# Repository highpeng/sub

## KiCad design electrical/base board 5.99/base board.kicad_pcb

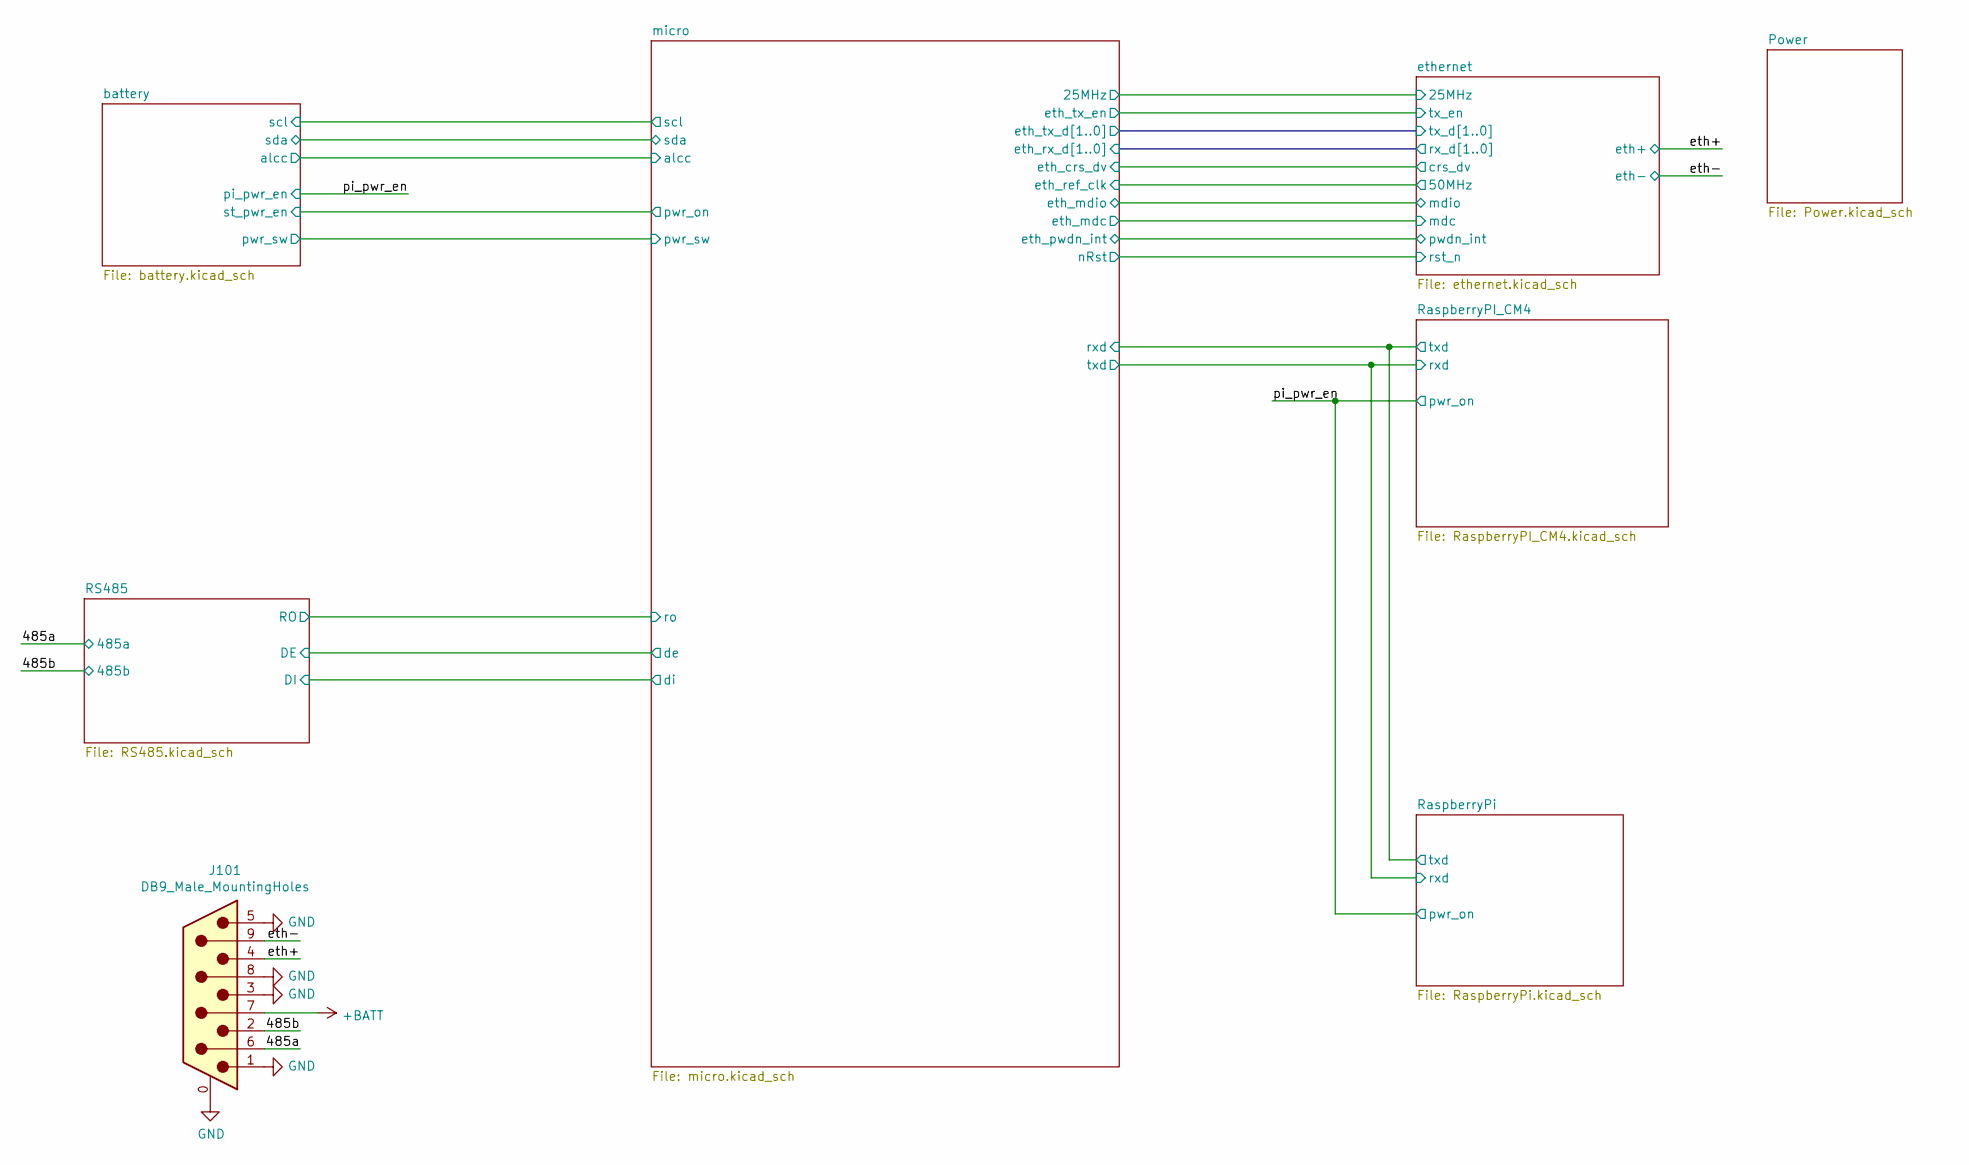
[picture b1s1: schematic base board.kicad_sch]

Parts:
J101: DB9_Male_MountingHoles; DSUB-9_Male_Horizontal_P2.77x2.84mm_EdgePinOffset9.90mm_Hou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

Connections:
+BATT: J101.7; also elsewhere on the board
/485a: J101.6; also elsewhere on the board
/485b: J101.2; also elsewhere on the board
/eth+: J101.4; also elsewhere on the board
/eth-: J101.9; also elsewhere on the board
GND: J101.0 (PAD), J101.1, J101.3, J101.5, J101.8; also elsewhere on the board

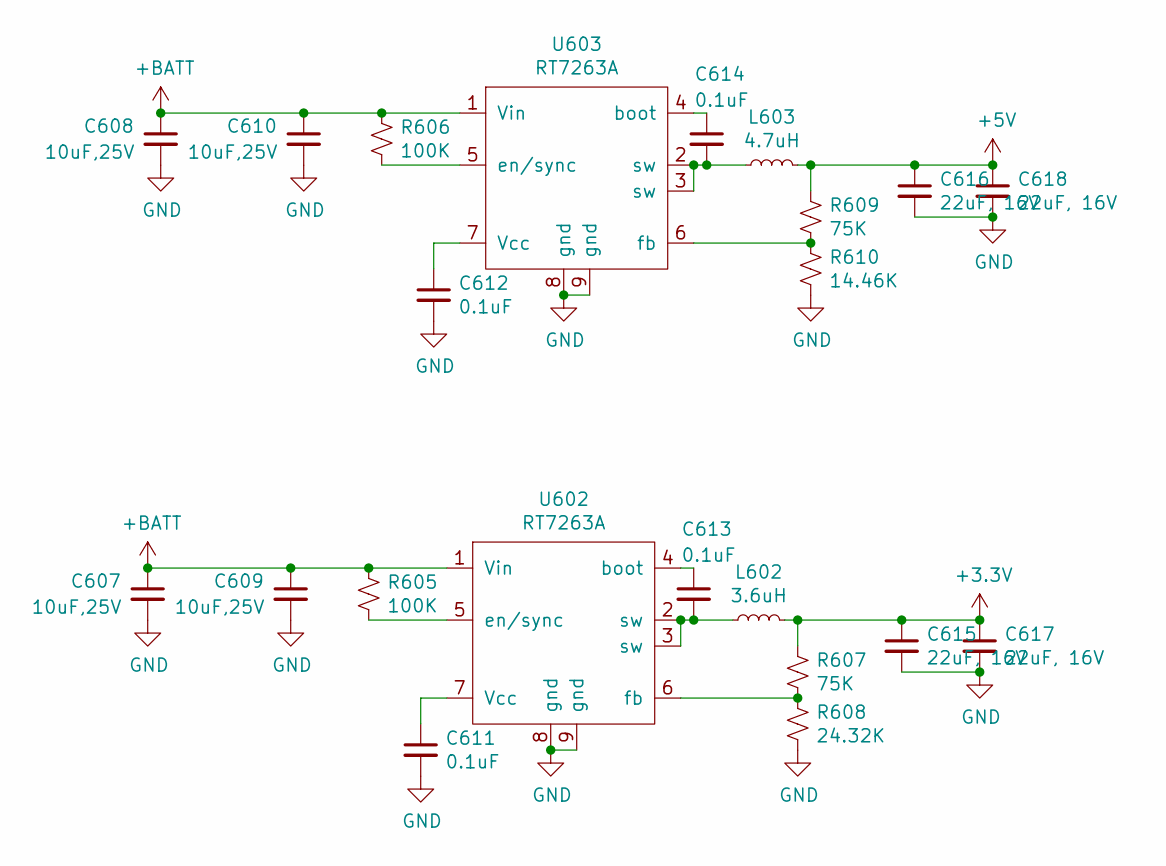
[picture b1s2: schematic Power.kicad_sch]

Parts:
C607, C608, C609, C610: 10uF,25V; C_1206_3216Metric
C611, C612, C613, C614: 0.1uF; C_0402_1005Metric
C615, C616, C617, C618: 22uF, 16V; C_1210_3225Metric
L602: 3.6uH; NR8040
L603: 4.7uH; NR8040
R605, R606: 100K; R_0402_1005Metric
R607, R609: 75K; R_0402_1005Metric
R608: 24.32K; R_0402_1005Metric
R610: 14.46K; R_0402_1005Metric
U602, U603: RT7263A; SOP-EP-8_3.9x4.9mm_P1.27mm

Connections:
+3V3: C615.1, C617.1, L602.2, R607.1; also elsewhere on the board
+5V: C616.1, C618.1, L603.2, R609.1; also elsewhere on the board
+BATT: C607.1, C608.1, C609.1, C610.1, R605.1, R606.1, U602.1 (Vin), U603.1 (Vin); also elsewhere on the board
GND: C607.2, C608.2, C609.2, C610.2, C611.2, C612.2, C615.2, C616.2, C617.2, C618.2, R608.2, R610.2, U602.8 (gnd), U602.9 (gnd), U603.8 (gnd), U603.9 (gnd); also elsewhere on the board
unnamed: C611.1, U602.7 (Vcc)
unnamed: C612.1, U603.7 (Vcc)
unnamed: C613.1, U602.4 (boot)
unnamed: C613.2, L602.1, U602.2 (sw), U602.3 (sw)
unnamed: C614.1, U603.4 (boot)
unnamed: C614.2, L603.1, U603.2 (sw), U603.3 (sw)
unnamed: R605.2, U602.5 (en/sync)
unnamed: R606.2, U603.5 (en/sync)
unnamed: R607.2, R608.1, U602.6 (fb)
unnamed: R609.2, R610.1, U603.6 (fb)

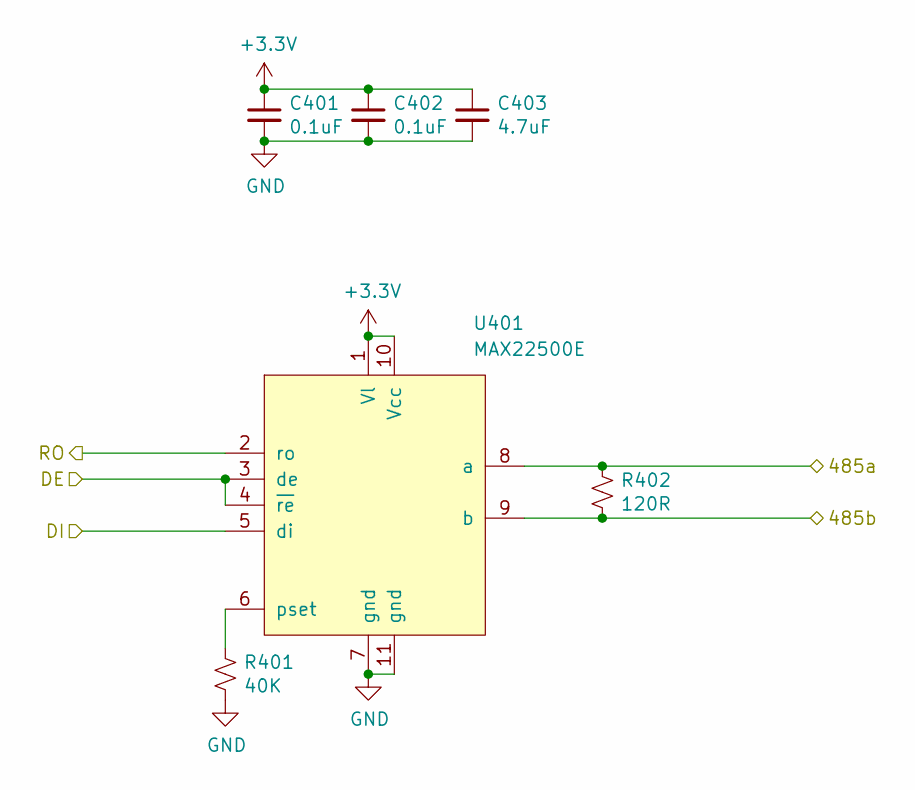
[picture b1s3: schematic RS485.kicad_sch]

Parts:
C401, C402: 0.1uF; C_0402_1005Metric
C403: 4.7uF; C_0603_1608Metric
R401: 40K; R_0402_1005Metric
R402: 120R; R_1206_3216Metric
U401: MAX22500E; DFN-10-1EP_3x3mm_P0.5mm_EP1.55x2.48mm

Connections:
+3V3: C401.1, C402.1, C403.1, U401.1 (Vl), U401.10 (Vcc); also elsewhere on the board
/485a: R402.1, U401.8 (a); also elsewhere on the board
/485b: R402.2, U401.9 (b); also elsewhere on the board
/RS485/DE: U401.3 (de~), U401.4 (~re); also elsewhere on the board
/RS485/DI: U401.5 (di); also elsewhere on the board
/RS485/RO: U401.2 (ro); also elsewhere on the board
GND: C401.2, C402.2, C403.2, R401.2, U401.7 (gnd), U401.11 (gnd); also elsewhere on the board
unnamed: R401.1, U401.6 (pset)

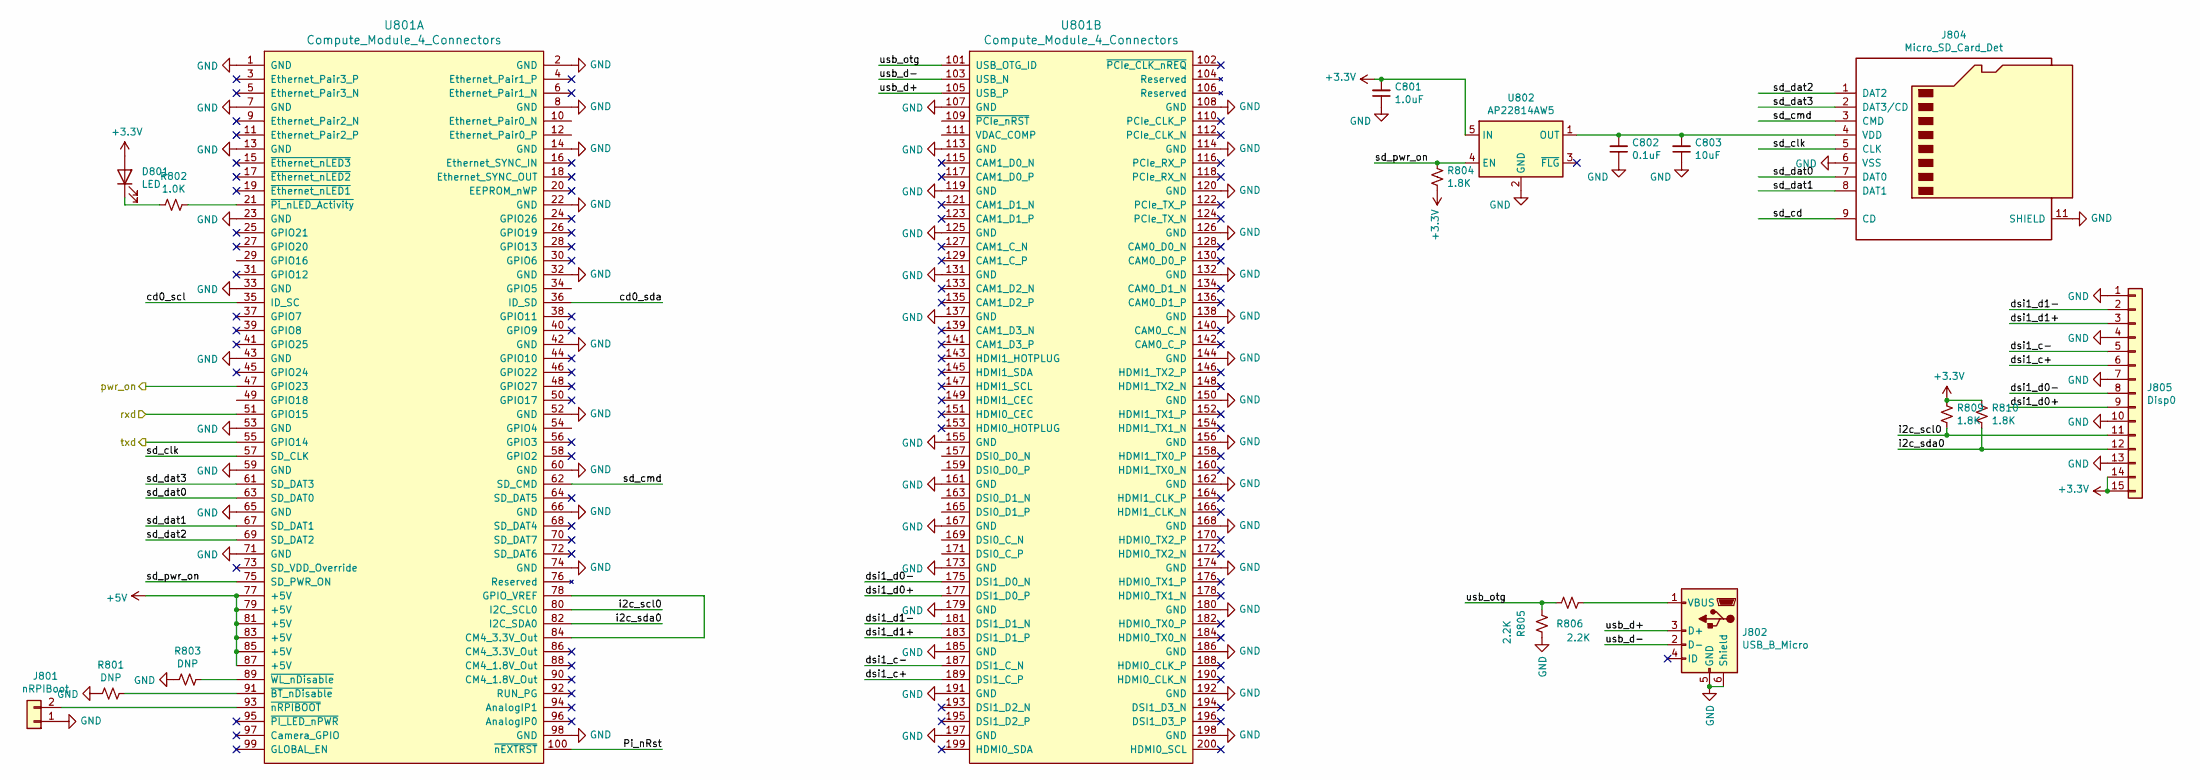
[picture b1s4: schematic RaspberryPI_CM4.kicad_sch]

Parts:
C801: 1.0uF; C_0603_1608Metric
C802: 0.1uF; C_0402_1005Metric
C803: 10uF; C_0805_2012Metric
D801: LED; LED_0402_1005Metric
J801: nRPIBoot; PinHeader_1x02_P1.27mm_Vertical
J802: USB_B_Micro; USB_Micro-B_Wuerth_629105150521
J804: Micro_SD_Card_Det; MEM2061
J805: Disp0; Molex_200528-0150_1x15-1MP_P1.00mm_Horizontal
R801, R803: DNP; R_0402_1005Metric
R802: 1.0K; R_0402_1005Metric
R804, R809, R810: 1.8K; R_0402_1005Metric
R805, R806: 2.2K; R_0402_1005Metric
U801: Compute_Module_4_Connectors; CM4
U802: AP22814AW5; SOT-23-5

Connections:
+3V3: C801.2, D801.2 (A), J805.14, J805.15, R804.2, R809.1, R810.1, U802.5 (IN); also elsewhere on the board
+5V: U801.77 (+5V), U801.79 (+5V), U801.81 (+5V), U801.83 (+5V), U801.85 (+5V), U801.87 (+5V); also elsewhere on the board
/RaspberryPI_CM4/Pi_nRst: U801.100 (~nEXTRST)
/RaspberryPI_CM4/cd0_scl: U801.35 (ID_SC)
/RaspberryPI_CM4/cd0_sda: U801.36 (ID_SD)
/RaspberryPI_CM4/dsi1_c+: J805.6, U801.189 (DSI1_C_P)
/RaspberryPI_CM4/dsi1_c-: J805.5, U801.187 (DSI1_C_N)
/RaspberryPI_CM4/dsi1_d0+: J805.9, U801.177 (DSI1_D0_P)
/RaspberryPI_CM4/dsi1_d0-: J805.8, U801.175 (DSI1_D0_N)
/RaspberryPI_CM4/dsi1_d1+: J805.3, U801.183 (DSI1_D1_P)
/RaspberryPI_CM4/dsi1_d1-: J805.2, U801.181 (DSI1_D1_N)
/RaspberryPI_CM4/i2c_scl0: J805.11, R809.2, U801.80 (I2C_SCL0)
/RaspberryPI_CM4/i2c_sda0: J805.12, R810.2, U801.82 (I2C_SDA0)
/RaspberryPI_CM4/rxd: U801.51 (GPIO15); also elsewhere on the board
/RaspberryPI_CM4/sd_cd: J804.9 (CD)
/RaspberryPI_CM4/sd_clk: J804.5 (CLK), U801.57 (SD_CLK)
/RaspberryPI_CM4/sd_cmd: J804.3 (CMD), U801.62 (SD_CMD)
/RaspberryPI_CM4/sd_dat0: J804.7 (DAT0), U801.63 (SD_DAT0)
/RaspberryPI_CM4/sd_dat1: J804.8 (DAT1), U801.67 (SD_DAT1)
/RaspberryPI_CM4/sd_dat2: J804.1 (DAT2), U801.69 (SD_DAT2)
/RaspberryPI_CM4/sd_dat3: J804.2 (DAT3/CD), U801.61 (SD_DAT3)
/RaspberryPI_CM4/sd_pwr_on: R804.1, U801.75 (SD_PWR_ON), U802.4 (EN)
/RaspberryPI_CM4/txd: U801.55 (GPIO14); also elsewhere on the board
/RaspberryPI_CM4/usb_d+: J802.3 (D+), U801.105 (USB_P)
/RaspberryPI_CM4/usb_d-: J802.2 (D-), U801.103 (USB_N)
/RaspberryPI_CM4/usb_otg: R805.1, R806.1, U801.101 (USB_OTG_ID)
/pi_pwr_en: U801.47 (GPIO23); also elsewhere on the board
GND: C801.1, C802.1, C803.1, J801.1, J802.5 (GND), J802.6 (Shield), J804.6 (VSS), J804.11 (SHIELD), J805.1, J805.4, J805.7, J805.10, J805.13, R801.2, R803.2, R805.2, U801.1 (GND), U801.2 (GND), U801.7 (GND), U801.8 (GND), U801.13 (GND), U801.14 (GND), U801.22 (GND), U801.23 (GND), U801.32 (GND), U801.33 (GND), U801.42 (GND), U801.43 (GND), U801.52 (GND), U801.53 (GND), U801.59 (GND), U801.60 (GND), U801.65 (GND), U801.66 (GND), U801.71 (GND), U801.74 (GND), U801.98 (GND), U801.107 (GND), U801.108 (GND), U801.113 (GND), U801.114 (GND), U801.119 (GND), U801.120 (GND), U801.125 (GND), U801.126 (GND), U801.131 (GND), U801.132 (GND), U801.137 (GND), U801.138 (GND), U801.144 (GND), U801.150 (GND), U801.155 (GND), U801.156 (GND), U801.161 (GND), U801.162 (GND), U801.167 (GND), U801.168 (GND), U801.173 (GND), U801.174 (GND), U801.179 (GND), U801.180 (GND), U801.185 (GND), U801.186 (GND), U801.191 (GND), U801.192 (GND), U801.197 (GND), U801.198 (GND), U802.2 (GND); also elsewhere on the board
unnamed: C802.2, C803.2, J804.4 (VDD), U802.1 (OUT)
unnamed: D801.1 (K), R802.2
unnamed: J801.2, U801.93 (~nRPIBOOT)
unnamed: J802.1 (VBUS), R806.2
unnamed: R801.1, U801.91 (~BT_nDisable)
unnamed: R802.1, U801.21 (~Pi_nLED_Activity)
unnamed: R803.1, U801.89 (~WL_nDisable)
unnamed: U801.78 (GPIO_VREF), U801.84 (CM4_3.3V_Out)

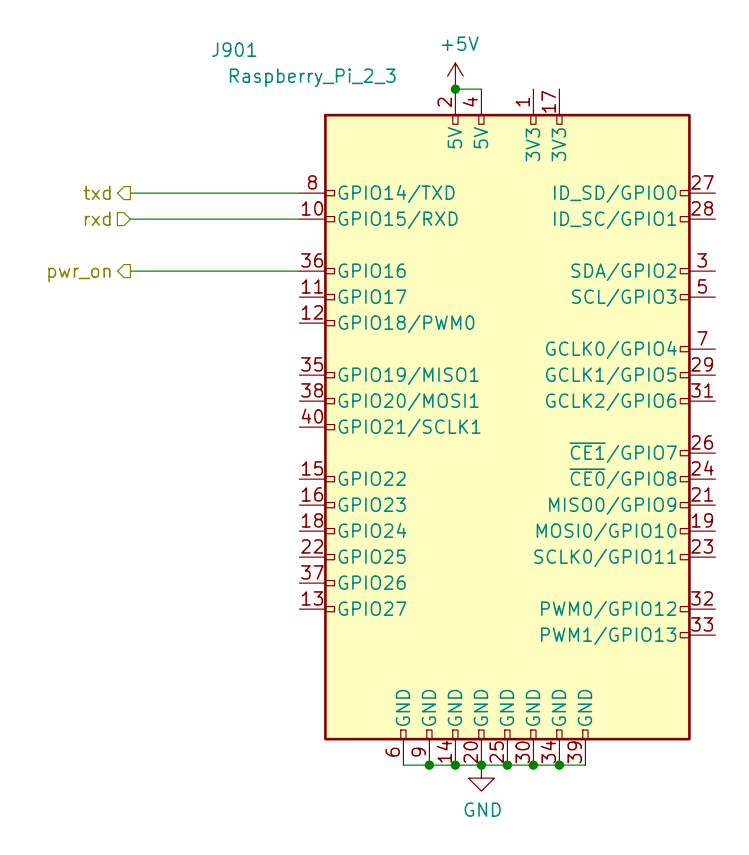
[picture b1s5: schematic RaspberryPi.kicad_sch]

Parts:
J901: Raspberry_Pi_2_3; MODULE_RASPBERRY_PI_3_MODEL_B+

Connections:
+5V: J901.2 (5V), J901.4 (5V); also elsewhere on the board
/RaspberryPI_CM4/rxd: J901.10 (GPIO15/RXD); also elsewhere on the board
/RaspberryPI_CM4/txd: J901.8 (GPIO14/TXD); also elsewhere on the board
/pi_pwr_en: J901.36 (GPIO16); also elsewhere on the board
GND: J901.6 (GND), J901.9 (GND), J901.14 (GND), J901.20 (GND), J901.25 (GND), J901.30 (GND), J901.34 (GND), J901.39 (GND); also elsewhere on the board

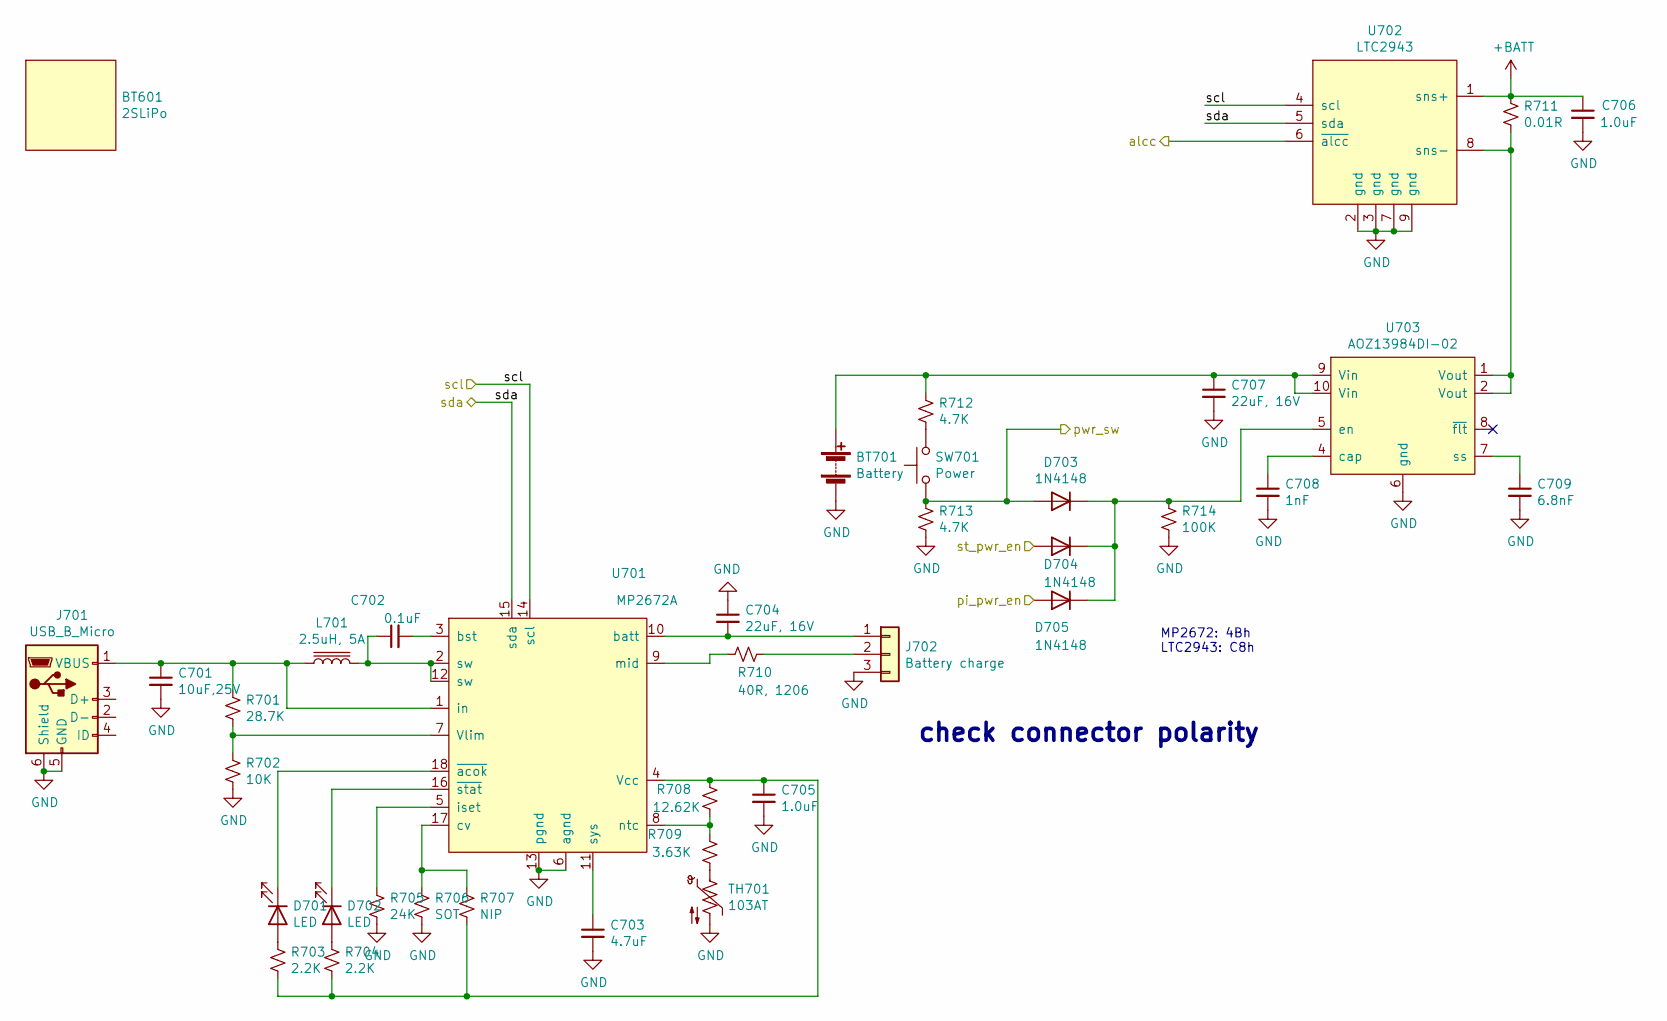
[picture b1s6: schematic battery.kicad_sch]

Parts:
BT601: 2SLiPo
BT701: Battery; AMASS_XT60-M
C701: 10uF,25V; C_1206_3216Metric
C702: 0.1uF; C_0402_1005Metric
C703: 4.7uF; C_0603_1608Metric
C704, C707: 22uF, 16V; C_1210_3225Metric
C705, C706: 1.0uF; C_0603_1608Metric
C708: 1nF; C_0402_1005Metric
C709: 6.8nF; C_0402_1005Metric
D701, D702: LED; LED_0402_1005Metric
D703, D704, D705: 1N4148; D_SOD-123
J701: USB_B_Micro; USB_Micro-B_Wuerth_629105150521
J702: Battery charge; JST_XH_B3B-XH-AM_1x03_P2.50mm_Vertical
L701: 2.5uH, 5A; CDRH8D38
R701: 28.7K; R_0402_1005Metric
R702: 10K; R_0402_1005Metric
R703, R704: 2.2K; R_0402_1005Metric
R705: 24K; R_0402_1005Metric
R706: SOT; R_0402_1005Metric
R707: NIP; R_0402_1005Metric
R708: 12.62K; R_0402_1005Metric
R709: 3.63K; R_0402_1005Metric
R710: 40R, 1206; R_1206_3216Metric
R711: 0.01R; R_0805_2012Metric
R712, R713: 4.7K; R_0402_1005Metric
R714: 100K; R_0402_1005Metric
SW701: Power; evqpf
TH701: 103AT; Hirose_DF13C_CL535-0402-2-51_1x02-1MP_P1.25mm_Vertical
U701: MP2672A; QFN-18
U702: LTC2943; DFN-8-1EP_3x3mm_P0.5mm_EP1.66x2.38mm
U703: AOZ13984DI-02; DFN3x3-12L

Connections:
+BATT: C706.1, R711.1, U702.1 (sns+); also elsewhere on the board
/battery/alcc: U702.6 (~alcc); also elsewhere on the board
/battery/pwr_sw: D703.2 (A), R713.1, SW701.1; also elsewhere on the board
/battery/scl: U701.14 (scl), U702.4 (scl); also elsewhere on the board
/battery/sda: U701.15 (sda), U702.5 (sda); also elsewhere on the board
/battery/st_pwr_en: D704.2 (A); also elsewhere on the board
/pi_pwr_en: D705.2 (A); also elsewhere on the board
GND: BT701.2 (-), C701.2, C703.2, C704.1, C705.2, C706.2, C707.2, C708.2, C709.2, J701.5 (GND), J701.6 (Shield), J702.3, R702.2, R705.2, R706.2, R713.2, R714.2, TH701.2, U701.6 (agnd), U701.13 (pgnd), U702.2 (gnd), U702.3 (gnd), U702.7 (gnd), U702.9 (gnd), U703.6 (gnd); also elsewhere on the board
unnamed: BT701.1 (+), C707.1, R712.1, U703.9 (Vin), U703.10 (Vin)
unnamed: C701.1, J701.1 (VBUS), L701.1, R701.1, U701.1 (in)
unnamed: C702.1, L701.2, U701.2 (sw), U701.12 (sw)
unnamed: C702.2, U701.3 (bst)
unnamed: C703.1, U701.11 (sys)
unnamed: C704.2, J702.1, U701.10 (batt)
unnamed: C705.1, R703.2, R704.2, R707.2, R708.2, U701.4 (Vcc)
unnamed: C708.1, U703.4 (cap)
unnamed: C709.1, U703.7 (ss)
unnamed: D701.1 (K), U701.18 (~acok)
unnamed: D701.2 (A), R703.1
unnamed: D702.1 (K), U701.16 (~stat)
unnamed: D702.2 (A), R704.1
unnamed: D703.1 (K), D704.1 (K), D705.1 (K), R714.1, U703.5 (en)
unnamed: J702.2, R710.1
unnamed: R701.2, R702.1, U701.7 (Vlim)
unnamed: R705.1, U701.5 (iset)
unnamed: R706.1, R707.1, U701.17 (cv)
unnamed: R708.1, R709.2, U701.8 (ntc)
unnamed: R709.1, TH701.1
unnamed: R710.2, U701.9 (mid)
unnamed: R711.2, U702.8 (sns-), U703.1 (Vout), U703.2 (Vout)
unnamed: R712.2, SW701.2

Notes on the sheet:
check connector polarity
MP2672: 4Bh LTC2943: C8h

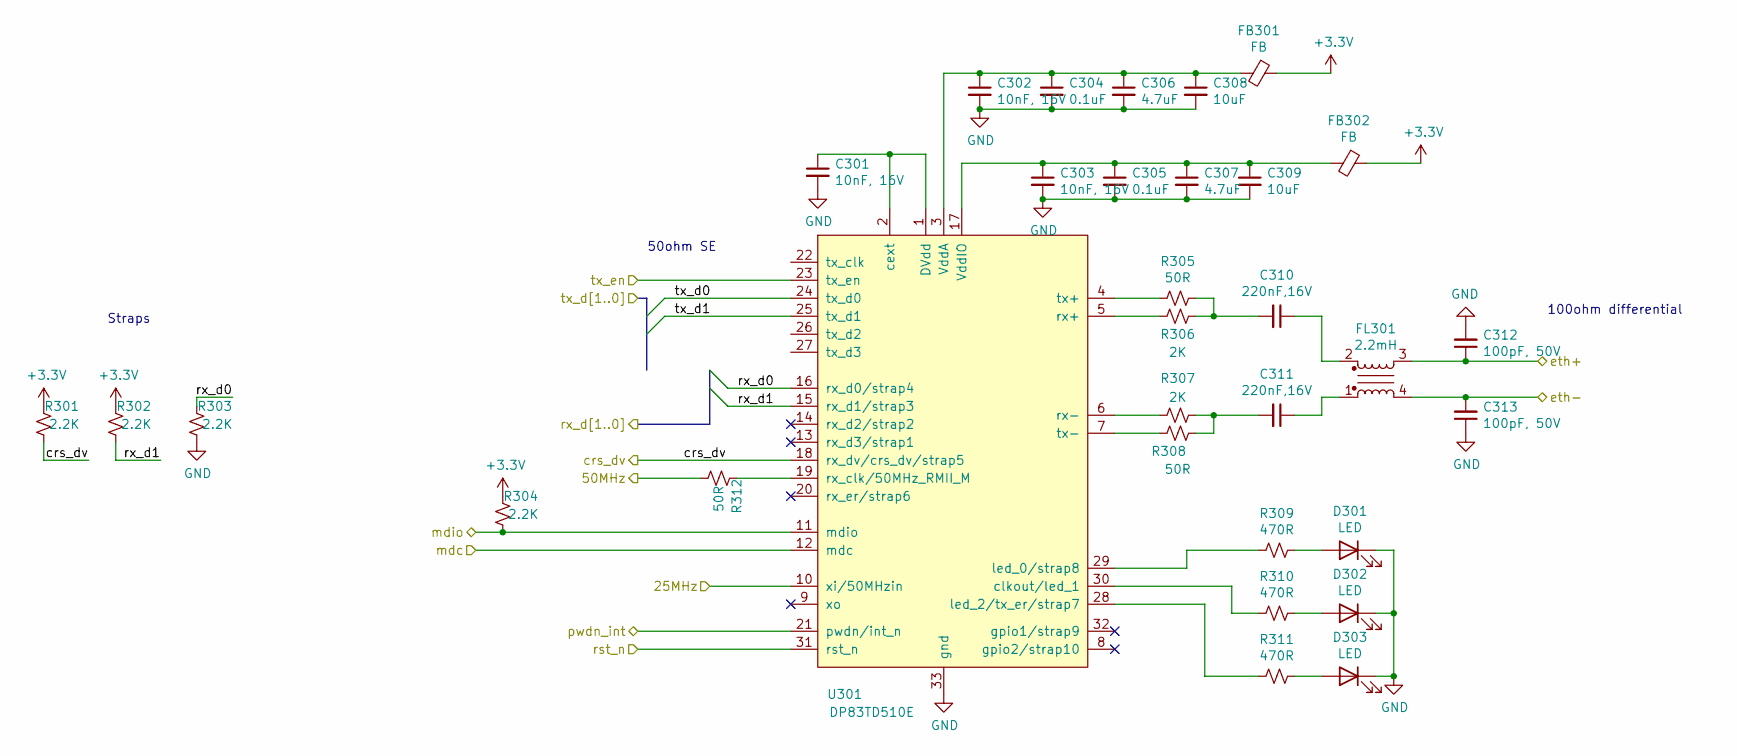
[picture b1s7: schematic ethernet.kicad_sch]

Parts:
C301, C302, C303: 10nF, 16V; C_0402_1005Metric
C304, C305: 0.1uF; C_0402_1005Metric
C306, C307: 4.7uF; C_0603_1608Metric
C308, C309: 10uF; C_0805_2012Metric
C310, C311: 220nF,16V; C_0603_1608Metric
C312, C313: 100pF, 50V; C_0603_1608Metric
D301, D302, D303: LED; LED_0402_1005Metric
FB301, FB302: FB; R_0603_1608Metric
FL301: 2.2mH; L_WE_SL5
R301, R302, R303, R304: 2.2K; R_0402_1005Metric
R305, R308, R312: 50R; R_0402_1005Metric
R306, R307: 2K; R_2512_6332Metric
R309, R310, R311: 470R; R_0402_1005Metric
U301: DP83TD510E; TQFN-32-1EP_5x5mm_P0.5mm_EP2.1x2.1mm

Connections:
+3V3: FB301.1, FB302.1, R301.2, R302.2, R304.2; also elsewhere on the board
/eth+: C312.1, FL301.3; also elsewhere on the board
/eth-: C313.2, FL301.4; also elsewhere on the board
/ethernet/25MHz: U301.10 (xi/50MHzin); also elsewhere on the board
/ethernet/50MHz: R312.1; also elsewhere on the board
/ethernet/crs_dv: R301.1, U301.18 (rx_dv/crs_dv/strap5); also elsewhere on the board
/ethernet/mdc: U301.12 (mdc); also elsewhere on the board
/ethernet/mdio: R304.1, U301.11 (mdio); also elsewhere on the board
/ethernet/pwdn_int: U301.21 (pwdn/int_n); also elsewhere on the board
/ethernet/tx_en: U301.23 (tx_en); also elsewhere on the board
/micro/eth_rx_d0: R303.2, U301.16 (rx_d0/strap4); also elsewhere on the board
/micro/eth_rx_d1: R302.1, U301.15 (rx_d1/strap3); also elsewhere on the board
/micro/eth_tx_d0: U301.24 (tx_d0); also elsewhere on the board
/micro/eth_tx_d1: U301.25 (tx_d1); also elsewhere on the board
/micro/nrst: U301.31 (rst_n); also elsewhere on the board
GND: C301.2, C302.2, C303.2, C304.2, C305.2, C306.2, C307.2, C308.2, C309.2, C312.2, C313.1, D301.1 (K), D302.1 (K), D303.1 (K), R303.1, U301.33 (gnd); also elsewhere on the board
unnamed: C301.1, U301.1 (DVdd), U301.2 (cext)
unnamed: C302.1, C304.1, C306.1, C308.1, FB301.2, U301.3 (VddA)
unnamed: C303.1, C305.1, C307.1, C309.1, FB302.2, U301.17 (VddIO)
unnamed: C310.1, FL301.2
unnamed: C310.2, R305.1, R306.1
unnamed: C311.1, FL301.1
unnamed: C311.2, R307.1, R308.1
unnamed: R305.2, U301.4 (tx+)
unnamed: R306.2, U301.5 (rx+)
unnamed: R307.2, U301.6 (rx-)
unnamed: R308.2, U301.7 (tx-)
unnamed: D301.2 (A), R309.1
unnamed: D302.2 (A), R310.1
unnamed: D303.2 (A), R311.1
unnamed: R312.2, U301.19 (rx_clk/50MHz_RMII_M)
unnamed: R311.2, U301.28 (led_2/tx_er/strap7)
unnamed: R309.2, U301.29 (led_0/strap8)
unnamed: R310.2, U301.30 (clkout/led_1)

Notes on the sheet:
Straps
50ohm SE
100ohm differential

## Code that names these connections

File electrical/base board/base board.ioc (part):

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Mcu.Name=STM32F217I(E-G)Tx
Mcu.Package=LQFP176
Mcu.UserName=STM32F217IETx
PA1.Mode=RMII
PA1.Signal=ETH_REF_CLK
PA11.Mode=Device_Only
PA11.Signal=USB_OTG_FS_DM
PA12.Mode=Device_Only
PA12.Signal=USB_OTG_FS_DP
PA13.Mode=JTAG_5_pins
PA13.Signal=SYS_JTMS-SWDIO
PA14.Mode=JTAG_5_pins
PA14.Signal=SYS_JTCK-SWCLK
PA15.Mode=JTAG_5_pins
PA15.Signal=SYS_JTDI
PA2.Mode=RMII
PA2.Signal=ETH_MDIO
PA3.Mode=Device_HS
PA3.Signal=USB_OTG_HS_ULPI_D0
PA5.Mode=Device_HS
PA5.Signal=USB_OTG_HS_ULPI_CK
PA6.GPIOParameters=GPIO_Label
PA6.GPIO_Label=fan
PA6.Signal=S_TIM13_CH1
PA7.Mode=RMII
PA7.Signal=ETH_CRS_DV
PA8.Mode=Clock-out-1
PA8.Signal=RCC_MCO_1
PA9.Mode=Activate_VBUS
PA9.Signal=USB_OTG_FS_VBUS
PB0.Mode=Device_HS
PB0.Signal=USB_OTG_HS_ULPI_D1
PB1.Mode=Device_HS
PB1.Signal=USB_OTG_HS_ULPI_D2
PB10.Mode=Device_HS
PB10.Signal=USB_OTG_HS_ULPI_D3
PB11.Mode=Device_HS
PB11.Signal=USB_OTG_HS_ULPI_D4
PB12.Mode=Device_HS
PB12.Signal=USB_OTG_HS_ULPI_D5
PB13.Mode=Device_HS
PB13.Signal=USB_OTG_HS_ULPI_D6
PB3.Mode=JTAG_5_pins
PB3.Signal=SYS_JTDO-SWO
PB4.Mode=JTAG_5_pins
PB4.Signal=SYS_JTRST
PB5.Mode=Device_HS
PB5.Signal=USB_OTG_HS_ULPI_D7
PB6.Mode=I2C
PB6.Signal=I2C1_SCL
PB7.Mode=I2C
PB7.Signal=I2C1_SDA
PB8.GPIOParameters=GPIO_Label
PB8.GPIO_Label=alcc
PB8.Signal=GPIO_Input
PB9.GPIOParameters=GPIO_Label
PB9.GPIO_Label=buzzer
PB9.Signal=S_TIM11_CH1
PC0.Mode=Device_HS
PC0.Signal=USB_OTG_HS_ULPI_STP
PC1.Mode=RMII
PC1.Signal=ETH_MDC
PC15-OSC32_OUT.GPIOParameters=GPIO_Label
PC15-OSC32_OUT.GPIO_Label=led
PC15-OSC32_OUT.Signal=GPIO_Output
PC2.Signal=ADCx_IN12
PC3.Signal=ADCx_IN13
PC4.Mode=RMII
PC4.Signal=ETH_RXD0
PC5.Mode=RMII
PC5.Signal=ETH_RXD1
PD5.Mode=Asynchronous
PD5.Signal=USART2_TX
PD6.Mode=Asynchronous
PD6.Signal=USART2_RX
PE2.GPIOParameters=GPIO_Label
PE2.GPIO_Label=joy1s
PE2.Signal=GPIO_Input
PE3.GPIOParameters=GPIO_Label
PE3.GPIO_Label=joy2s
PE3.Signal=GPIO_Input
PE4.GPIOParameters=GPIO_Label
PE4.GPIO_Label=joy3s
PE4.Signal=GPIO_Input
PE5.GPIOParameters=GPIO_Label
PE5.GPIO_Label=joy4s
PE5.Signal=GPIO_Input
PF0.GPIOParameters=GPIO_Pu
PF0.GPIO_Pu=GPIO_PULLUP
PF0.Mode=I2C
PF0.Signal=I2C2_SDA
PF1.GPIOParameters=GPIO_Pu
PF1.GPIO_Pu=GPIO_PULLUP
PF1.Mode=I2C
PF1.Signal=I2C2_SCL
PF10.GPIOParameters=GPIO_Label
PF10.GPIO_Label=joy4b
PF10.Mode=IN8
PF10.Signal=ADC3_IN8
PF3.GPIOParameters=GPIO_Label
PF3.GPIO_Label=joy1a
PF3.Mode=IN9
PF3.Signal=ADC3_IN9
PF4.GPIOParameters=GPIO_Label
PF4.GPIO_Label=joy1b
PF4.Mode=IN14
PF4.Signal=ADC3_IN14
PF5.GPIOParameters=GPIO_Label
PF5.GPIO_Label=joy2a
PF5.Mode=IN15
PF5.Signal=ADC3_IN15
PF6.GPIOParameters=GPIO_Label
PF6.GPIO_Label=joy2b
PF6.Mode=IN4
PF6.Signal=ADC3_IN4
PF7.GPIOParameters=GPIO_Label
PF7.GPIO_Label=joy3a
PF7.Mode=IN5
PF7.Signal=ADC3_IN5
PF8.GPIOParameters=GPIO_Label
PF8.GPIO_Label=joy3b
PF8.Mode=IN6
PF8.Signal=ADC3_IN6
PF9.GPIOParameters=GPIO_Label
PF9.GPIO_Label=joy4a
PF9.Mode=IN7
PF9.Signal=ADC3_IN7
PG11.Mode=RMII
PG11.Signal=ETH_TX_EN
PG13.Mode=RMII
PG13.Signal=ETH_TXD0
PG14.Mode=RMII
PG14.Signal=ETH_TXD1
PH0-OSC_IN.Mode=HSE-External-Clock-Source
PH0-OSC_IN.Signal=RCC_OSC_IN
PH1-OSC_OUT.Mode=HSE-External-Clock-Source
PH1-OSC_OUT.Signal=RCC_OSC_OUT
PH4.Mode=Device_HS
PH4.Signal=USB_OTG_HS_ULPI_NXT
PI11.Mode=Device_HS
PI11.Signal=USB_OTG_HS_ULPI_DIR
RCC.HSE_VALUE=25000000
RCC.SYSCLKFreq_VALUE=120000000
RCC.SYSCLKSource=RCC_SYSCLKSOURCE_PLLCLK
board=custom

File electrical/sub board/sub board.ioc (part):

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Mcu.Name=STM32F217I(E-G)Tx
Mcu.Package=LQFP176
Mcu.UserName=STM32F217IETx
PA0-WKUP.Signal=S_TIM2_CH1_ETR
PA1.Mode=RMII
PA1.Signal=ETH_REF_CLK
PA11.Mode=Device_Only
PA11.Signal=USB_OTG_FS_DM
PA12.Mode=Device_Only
PA12.Signal=USB_OTG_FS_DP
PA13.Mode=JTAG_5_pins
PA13.Signal=SYS_JTMS-SWDIO
PA14.Mode=JTAG_5_pins
PA14.Signal=SYS_JTCK-SWCLK
PA15.Mode=JTAG_5_pins
PA15.Signal=SYS_JTDI
PA2.Mode=RMII
PA2.Signal=ETH_MDIO
PA3.Mode=Device_HS
PA3.Signal=USB_OTG_HS_ULPI_D0
PA5.Mode=Device_HS
PA5.Signal=USB_OTG_HS_ULPI_CK
PA7.Mode=RMII
PA7.Signal=ETH_CRS_DV
PA8.Mode=Clock-out-1
PA8.Signal=RCC_MCO_1
PA9.Mode=Activate_VBUS
PA9.Signal=USB_OTG_FS_VBUS
PB0.Mode=Device_HS
PB0.Signal=USB_OTG_HS_ULPI_D1
PB1.Mode=Device_HS
PB1.Signal=USB_OTG_HS_ULPI_D2
PB10.Mode=Device_HS
PB10.Signal=USB_OTG_HS_ULPI_D3
PB11.Mode=Device_HS
PB11.Signal=USB_OTG_HS_ULPI_D4
PB12.Mode=Device_HS
PB12.Signal=USB_OTG_HS_ULPI_D5
PB13.Mode=Device_HS
PB13.Signal=USB_OTG_HS_ULPI_D6
PB14.Mode=Full_Duplex_Master
PB14.Signal=SPI2_MISO
PB15.Mode=Full_Duplex_Master
PB15.Signal=SPI2_MOSI
PB3.Mode=JTAG_5_pins
PB3.Signal=SYS_JTDO-SWO
PB4.Mode=JTAG_5_pins
PB4.Signal=SYS_JTRST
PB5.Mode=Device_HS
PB5.Signal=USB_OTG_HS_ULPI_D7
PB6.Mode=I2C
PB6.Signal=I2C1_SCL
PB7.Mode=I2C
PB7.Signal=I2C1_SDA
PB8.GPIOParameters=GPIO_Label
PB8.GPIO_Label=sonar_clk
PB8.Signal=S_TIM10_CH1
PB9.Mode=NSS_Signal_Hard_Input
PB9.Signal=SPI2_NSS
PC0.Mode=Device_HS
PC0.Signal=USB_OTG_HS_ULPI_STP
PC1.Mode=RMII
PC1.Signal=ETH_MDC
PC10.Mode=SD_4_bits_Wide_bus
PC10.Signal=SDIO_D2
PC11.Mode=SD_4_bits_Wide_bus
PC11.Signal=SDIO_D3
PC12.Mode=SD_4_bits_Wide_bus
PC12.Signal=SDIO_CK
PC13.Signal=GPIO_Input
PC15-OSC32_OUT.GPIOParameters=GPIO_Label
PC15-OSC32_OUT.GPIO_Label=led
PC15-OSC32_OUT.Signal=GPIO_Output
PC2.Signal=ADCx_IN12
PC4.Mode=RMII
PC4.Signal=ETH_RXD0
PC5.Mode=RMII
PC5.Signal=ETH_RXD1
PC6.GPIOParameters=GPIO_Label
PC6.GPIO_Label=sonar_out3
PC6.Signal=S_TIM8_CH1
PC7.GPIOParameters=GPIO_Label
PC7.GPIO_Label=sonar_out4
PC7.Signal=S_TIM8_CH2
PC8.Mode=SD_4_bits_Wide_bus
PC8.Signal=SDIO_D0
PC9.Mode=SD_4_bits_Wide_bus
PC9.Signal=SDIO_D1
PD12.GPIOParameters=GPIO_Label
PD12.GPIO_Label=bdlc0
PD12.Signal=S_TIM4_CH1
PD13.GPIOParameters=GPIO_Label
PD13.GPIO_Label=bdlc1
PD13.Signal=S_TIM4_CH2
PD14.GPIOParameters=GPIO_Label
PD14.GPIO_Label=bdlc2
PD14.Signal=S_TIM4_CH3
PD15.GPIOParameters=GPIO_Label
PD15.GPIO_Label=bdlc3
PD15.Signal=S_TIM4_CH4
PD2.Mode=SD_4_bits_Wide_bus
PD2.Signal=SDIO_CMD
PD4.Mode=RTS_Only
PD4.Signal=USART2_RTS
PD5.Mode=Asynchronous
PD5.Signal=USART2_TX
PD6.Mode=Asynchronous
PD6.Signal=USART2_RX
PD8.Mode=Asynchronous
PD8.Signal=USART3_TX
PD9.Mode=Asynchronous
PD9.Signal=USART3_RX
PE11.GPIOParameters=GPIO_Label
PE11.GPIO_Label=servo1
PE11.Signal=S_TIM1_CH2
PE13.GPIOParameters=GPIO_Label
PE13.GPIO_Label=servo2
PE13.Signal=S_TIM1_CH3
PE14.GPIOParameters=GPIO_Label
PE14.GPIO_Label=servo3
PE14.Signal=S_TIM1_CH4
PE5.GPIOParameters=GPIO_Label
PE5.GPIO_Label=lights
PE5.Signal=S_TIM9_CH1
PE9.GPIOParameters=GPIO_Label
PE9.GPIO_Label=servo0
PE9.Signal=S_TIM1_CH1
PF0.Mode=I2C
PF0.Signal=I2C2_SDA
PF1.Mode=I2C
PF1.Signal=I2C2_SCL
PF2.GPIOParameters=GPIO_Label
PF2.GPIO_Label=water
PF2.Signal=GPIO_Input
PF3.GPIOParameters=GPIO_Label
PF3.GPIO_Label=alcc0
PF3.Signal=GPIO_Input
PF4.GPIOParameters=GPIO_Label
PF4.GPIO_Label=alcc1
PF4.Signal=GPIO_Input
PF6.Mode=IN4
PF6.Signal=ADC3_IN4
PF7.Mode=IN5
PF7.Signal=ADC3_IN5
PF8.Mode=IN6
PF8.Signal=ADC3_IN6
PF9.Mode=IN7
PF9.Signal=ADC3_IN7
PG10.GPIOParameters=GPIO_Label
PG10.GPIO_Label=eth_pwd_int
PG10.Signal=GPIO_Input
PG11.Mode=RMII
PG11.Signal=ETH_TX_EN
PG13.Mode=RMII
PG13.Signal=ETH_TXD0
PG14.Mode=RMII
PG14.Signal=ETH_TXD1
PH0-OSC_IN.Mode=HSE-External-Clock-Source
PH0-OSC_IN.Signal=RCC_OSC_IN
PH1-OSC_OUT.Mode=HSE-External-Clock-Source
PH1-OSC_OUT.Signal=RCC_OSC_OUT
PH10.GPIOParameters=GPIO_Label
PH10.GPIO_Label=bdlc4
PH10.Signal=S_TIM5_CH1
PH11.GPIOParameters=GPIO_Label
PH11.GPIO_Label=bdlc5
PH11.Signal=S_TIM5_CH2
PH12.GPIOParameters=GPIO_Label
PH12.GPIO_Label=bdlc6
PH12.Signal=S_TIM5_CH3
PH4.Mode=Device_HS
PH4.Signal=USB_OTG_HS_ULPI_NXT
PH6.GPIOParameters=GPIO_Label
PH6.GPIO_Label=sonar_clk_in
PH6.Signal=S_TIM12_CH1
PH7.Mode=I2C
PH7.Signal=I2C3_SCL
PH8.Mode=I2C
PH8.Signal=I2C3_SDA
PI0.GPIOParameters=GPIO_Label
PI0.GPIO_Label=bdlc7
PI0.Signal=S_TIM5_CH4
PI1.Mode=Full_Duplex_Master
PI1.Signal=SPI2_SCK
PI11.Mode=Device_HS
PI11.Signal=USB_OTG_HS_ULPI_DIR
PI4.GPIOParameters=GPIO_Label
PI4.GPIO_Label=sonar_io1
PI4.Signal=GPIO_Output
PI5.GPIOParameters=GPIO_Label
PI5.GPIO_Label=sonar_sel
PI5.Signal=GPIO_Output
PI6.GPIOParameters=GPIO_Label
PI6.GPIO_Label=sonar_pwr
PI6.Signal=GPIO_Output
RCC.HSE_VALUE=25000000
RCC.SYSCLKFreq_VALUE=120000000
RCC.SYSCLKSource=RCC_SYSCLKSOURCE_PLLCLK
board=custom
